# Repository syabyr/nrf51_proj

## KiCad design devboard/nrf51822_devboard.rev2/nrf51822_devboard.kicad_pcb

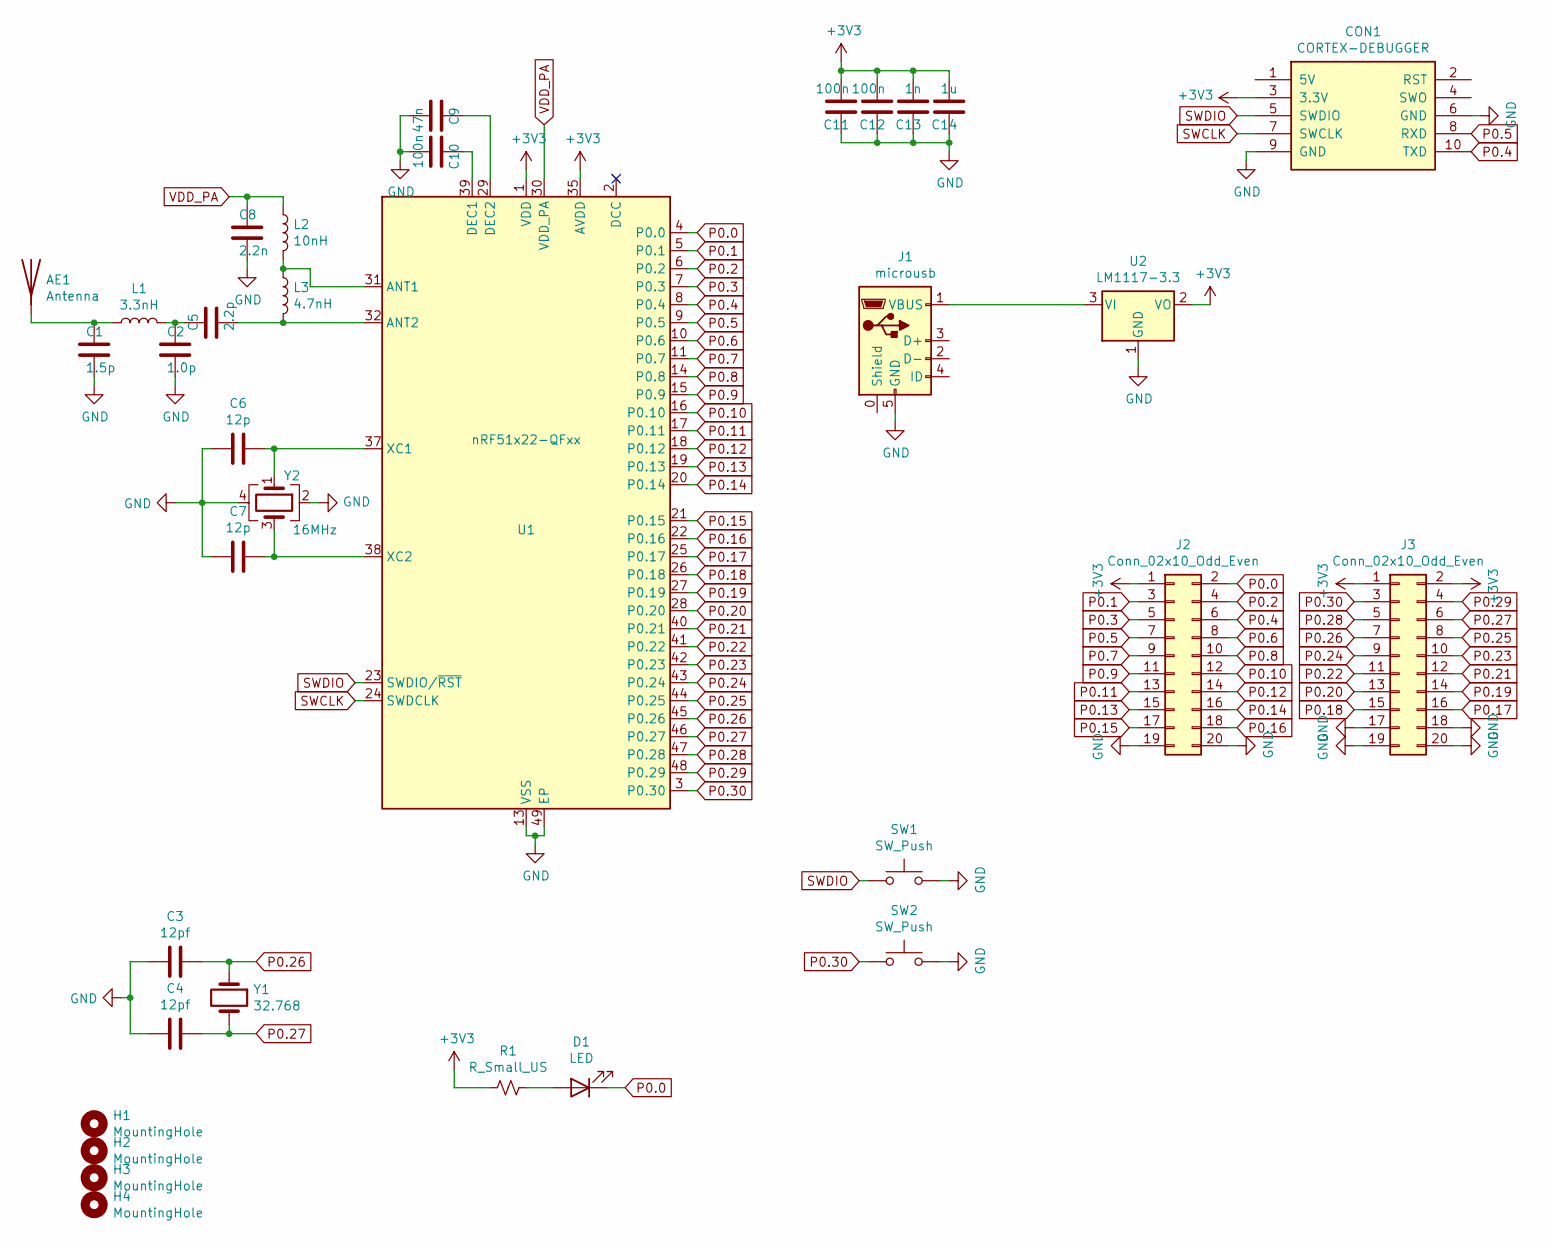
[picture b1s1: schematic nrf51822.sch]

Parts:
AE1: Antenna; Johanson_2450AT43F0100
C1: 1.5p; C_0402_1005Metric_Pad0.74x0.62mm_HandSolder
C2: 1.0p; C_0402_1005Metric_Pad0.74x0.62mm_HandSolder
C3, C4: 12pf; C_0402_1005Metric_Pad0.74x0.62mm_HandSolder
C5: 2.2p; C_0402_1005Metric_Pad0.74x0.62mm_HandSolder
C6, C7: 12p; C_0402_1005Metric_Pad0.74x0.62mm_HandSolder
C8: 2.2n; C_0402_1005Metric_Pad0.74x0.62mm_HandSolder
C9: 47n; C_0402_1005Metric_Pad0.74x0.62mm_HandSolder
C10, C11, C12: 100n; C_0402_1005Metric_Pad0.74x0.62mm_HandSolder
C13: 1n; C_0402_1005Metric_Pad0.74x0.62mm_HandSolder
C14: 1u; C_0603_1608Metric_Pad1.08x0.95mm_HandSolder
CON1: CORTEX-DEBUGGER; debugger_2x05_P1.27mm_Vertical
D1: LED; LED_0603_1608Metric_Pad1.05x0.95mm_HandSolder
H1, H2, H3, H4: MountingHole; MountingHole_3.2mm_M3_ISO7380
J1: microusb; USB_Micro-B_Wuerth_629105150521_CircularHoles
J2, J3: Conn_02x10_Odd_Even; PinHeader_2x10_P2.54mm_Vertical
L1: 3.3nH; L_0402_1005Metric_Pad0.77x0.64mm_HandSolder
L2: 10nH; L_0402_1005Metric_Pad0.77x0.64mm_HandSolder
L3: 4.7nH; L_0402_1005Metric_Pad0.77x0.64mm_HandSolder
R1: R_Small_US; R_0402_1005Metric_Pad0.72x0.64mm_HandSolder
SW1, SW2: SW_Push; turtlekey
U1: nRF51x22-QFxx; QFN-48-1EP_6x6mm_P0.4mm_EP4.6x4.6mm
U2: LM1117-3.3; SOT-223-3_TabPin2
Y1: 32.768; Crystal_SMD_G8-2Pin_3.2x1.5mm_HandSoldering
Y2: 16MHz; Crystal_SMD_3225-4Pin_3.2x2.5mm

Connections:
+3V3: C11.2, C12.2, C13.2, C14.2, CON1.3 (3.3V), J2.1, J3.1, J3.2, R1.2, U1.1 (VDD), U1.12 (VDD), U1.35 (AVDD), U1.36 (AVDD), U2.2 (VO)
GND: C1.2, C2.2, C3.2, C4.2, C6.2, C7.2, C8.2, C9.2, C10.2, C11.1, C12.1, C13.1, C14.1, CON1.6 (GND), CON1.9 (GND), J1.5 (GND), J2.19, J2.20, J3.17, J3.18, J3.19, J3.20, SW1.2, SW2.2, U1.13 (VSS), U1.33 (VSS), U1.34 (VSS), U1.49 (EP), U2.1 (GND), Y2.2, Y2.4
unnamed: AE1.1, C1.1, L1.1
unnamed: C2.1, C5.1, L1.2
unnamed: C5.2, L3.2, U1.32 (ANT2)
unnamed: C6.1, U1.37 (XC1), Y2.1
unnamed: C7.1, U1.38 (XC2), Y2.3
unnamed: C9.1, U1.29 (DEC2)
unnamed: C10.1, U1.39 (DEC1)
unnamed: D1.2 (A), R1.1
unnamed: J1.1 (VBUS), U2.3 (VI)
unnamed: L2.2, L3.1, U1.31 (ANT1)
P0.0: D1.1 (K), J2.2, U1.4 (P0.0)
P0.1: J2.3, U1.5 (P0.1)
P0.2: J2.4, U1.6 (P0.2)
P0.3: J2.5, U1.7 (P0.3)
P0.4: CON1.10 (TXD), J2.6, U1.8 (P0.4)
P0.5: CON1.8 (RXD), J2.7, U1.9 (P0.5)
P0.6: J2.8, U1.10 (P0.6)
P0.7: J2.9, U1.11 (P0.7)
P0.8: J2.10, U1.14 (P0.8)
P0.9: J2.11, U1.15 (P0.9)
P0.10: J2.12, U1.16 (P0.10)
P0.11: J2.13, U1.17 (P0.11)
P0.12: J2.14, U1.18 (P0.12)
P0.13: J2.15, U1.19 (P0.13)
P0.14: J2.16, U1.20 (P0.14)
P0.15: J2.17, U1.21 (P0.15)
P0.16: J2.18, U1.22 (P0.16)
P0.17: J3.16, U1.25 (P0.17)
P0.18: J3.15, U1.26 (P0.18)
P0.19: J3.14, U1.27 (P0.19)
P0.20: J3.13, U1.28 (P0.20)
P0.21: J3.12, U1.40 (P0.21)
P0.22: J3.11, U1.41 (P0.22)
P0.23: J3.10, U1.42 (P0.23)
P0.24: J3.9, U1.43 (P0.24)
P0.25: J3.8, U1.44 (P0.25)
P0.26: C3.1, J3.7, U1.45 (P0.26), Y1.1
P0.27: C4.1, J3.6, U1.46 (P0.27), Y1.2
P0.28: J3.5, U1.47 (P0.28)
P0.29: J3.4, U1.48 (P0.29)
P0.30: J3.3, SW2.1, U1.3 (P0.30)
SWCLK: CON1.7 (SWCLK), U1.24 (SWDCLK)
SWDIO: CON1.5 (SWDIO), SW1.1, U1.23 (SWDIO/~RST)
VDD_PA: C8.1, L2.1, U1.30 (VDD_PA)

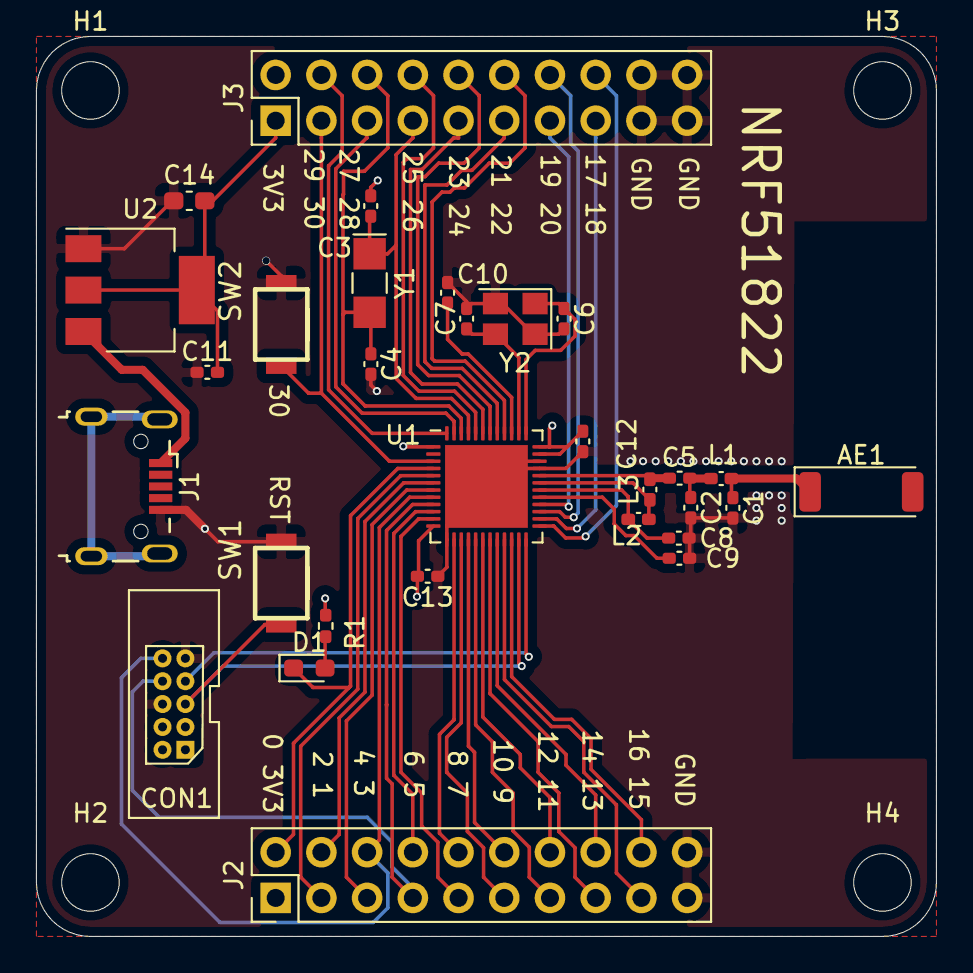
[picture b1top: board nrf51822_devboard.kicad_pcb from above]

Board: 4 copper layers, 50.0 x 50.0 mm, 34 parts (0 on the bottom side), 46 nets.

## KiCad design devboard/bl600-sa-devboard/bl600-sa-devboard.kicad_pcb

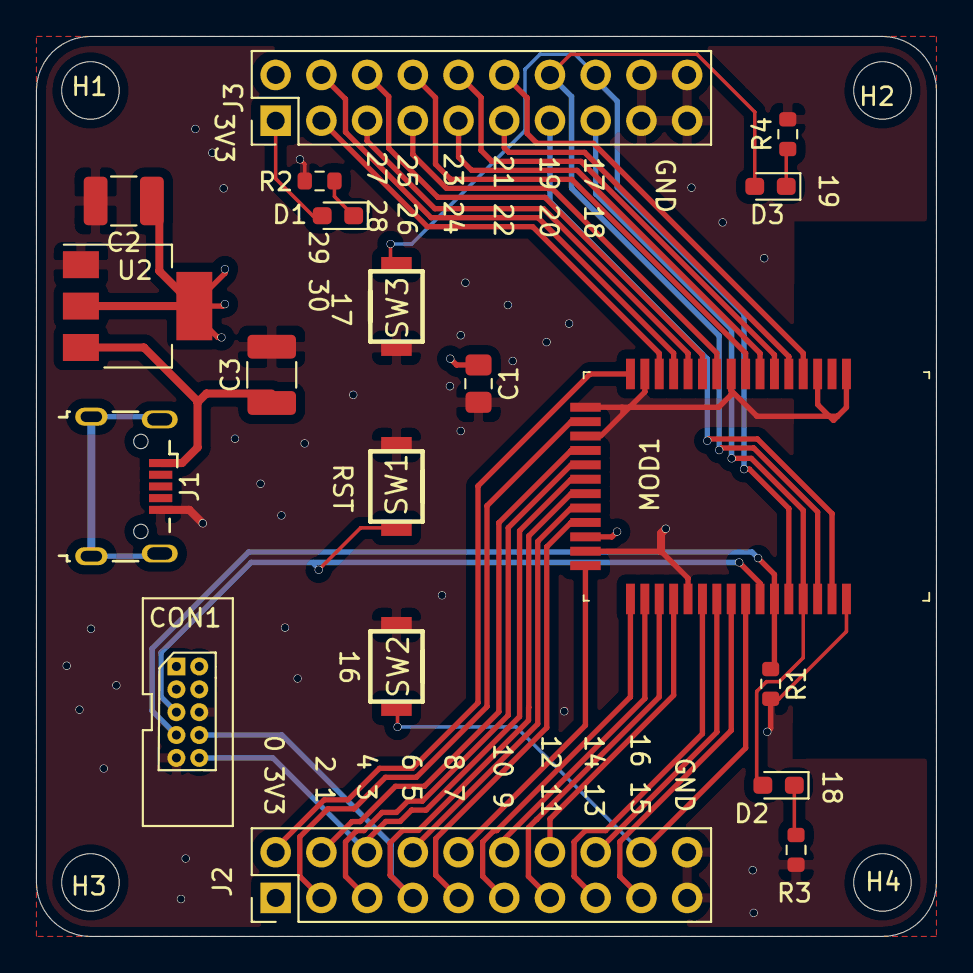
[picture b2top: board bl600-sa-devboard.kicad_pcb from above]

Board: 4 copper layers, 50.0 x 50.0 mm, 23 parts (0 on the bottom side), 39 nets.

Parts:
C1: C_Small; C_0805_2012Metric_Pad1.18x1.45mm_HandSolder
C2, C3: C_Small; C_1210_3225Metric_Pad1.33x2.70mm_HandSolder
CON1: CORTEX-DEBUGGER; debugger_2x05_P1.27mm_Vertical
D1, D2, D3: LED; LED_0603_1608Metric_Pad1.05x0.95mm_HandSolder
H1, H2, H3, H4: MountingHole; MountingHole_3.2mm_M3
J1: microusb; USB_Micro-B_Wuerth_629105150521_CircularHoles
J2, J3: Conn_02x10_Odd_Even; PinHeader_2x10_P2.54mm_Vertical
MOD1: BL600-SA; BLUETOOTH_MODULE_BL600-SA
R1, R2, R3, R4: 12K; R_0603_1608Metric
SW1, SW2, SW3: SW_Push; turtlekey
U2: LM1117-3.3; SOT-223-3_TabPin2

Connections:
+3V3: C1.1, C2.1, CON1.3, D1.2, J2.1, J3.1, J3.2, MOD1.10, U2.2
GND: C1.2, C2.2, C3.2, CON1.6, CON1.9, J1.5, J2.19, J2.20, J3.17, J3.18, J3.19, J3.20, MOD1.1, MOD1.3, MOD1.11, MOD1.17, MOD1.28, MOD1.29, MOD1.31, MOD1.37, MOD1.43, R1.2, R2.2, R3.2, R4.2, SW1.2, SW2.2, SW3.2, U2.1
IO_0: J2.2, MOD1.44
IO_1: J2.3, MOD1.2
IO_2: J2.4, MOD1.4
IO_3: J2.5, MOD1.5
IO_4: CON1.10, J2.6, MOD1.6
IO_5: CON1.8, J2.7, MOD1.7
IO_6: J2.8, MOD1.8
IO_7: J2.9, MOD1.9
IO_8: J2.10, MOD1.12
IO_9: J2.11, MOD1.13
IO_10: J2.12, MOD1.14
IO_11: J2.13, MOD1.15
IO_12: J2.14, MOD1.16
IO_13: J2.15, MOD1.18
IO_14: J2.16, MOD1.19
IO_15: J2.17, MOD1.20
IO_16: J2.18, MOD1.21, SW2.1
IO_17: J3.16, MOD1.24, SW3.1
IO_18: D2.2, J3.15, MOD1.25
IO_19: D3.2, J3.14, MOD1.26
IO_20: J3.13, MOD1.27
IO_21: J3.12, MOD1.32
IO_22: J3.11, MOD1.33
IO_23: J3.10, MOD1.34
IO_24: J3.9, MOD1.35
IO_25: J3.8, MOD1.36
IO_26: J3.7, MOD1.38
IO_27: J3.6, MOD1.39
IO_28: J3.5, MOD1.40
IO_29: J3.4, MOD1.41
IO_30: J3.3, MOD1.42
unnamed: D1.1, R2.1
unnamed: D2.1, R3.1
unnamed: D3.1, R4.1
SWCLK: CON1.7, MOD1.23, R1.1
SWDIO: CON1.5, MOD1.22, SW1.1
VBUS: C3.1, J1.1, U2.3

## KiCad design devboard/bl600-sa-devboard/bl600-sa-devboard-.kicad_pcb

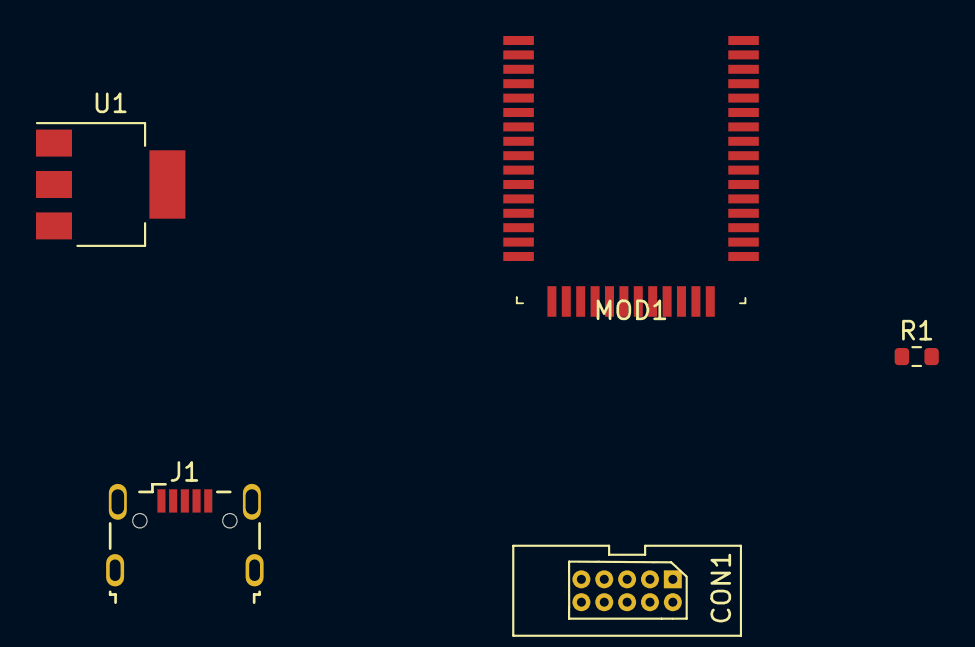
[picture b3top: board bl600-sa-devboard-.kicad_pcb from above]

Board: 2 copper layers, 5 parts (0 on the bottom side), 7 nets, no tracks yet.

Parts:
CON1: CORTEX-DEBUGGER; debugger_2x05_P1.27mm_Vertical
J1: microusb; USB_Micro-B_Wuerth_629105150521_CircularHoles
MOD1: BL600-SA; BLUETOOTH_MODULE_BL600-SA
R1: 12K; R_0603_1608Metric
U1: LM1117-3.3; SOT-223-3_TabPin2

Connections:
+3V3: CON1.3, MOD1.10, U1.2
GND: CON1.6, CON1.9, J1.5, MOD1.1, MOD1.3, MOD1.11, MOD1.17, MOD1.28, MOD1.29, MOD1.31, MOD1.37, MOD1.43, R1.2, U1.1
IO_4: CON1.10, MOD1.6
IO_5: CON1.8, MOD1.7
SWCLK: CON1.7, MOD1.23, R1.1
SWDIO: CON1.5, MOD1.22
VBUS: J1.1, U1.3

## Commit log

2021-12-09 orig
2021-12-09 helloworld
2021-12-09 cmake
2021-12-10 ld fix
2021-12-10 ble ok
2022-01-30 devboard
2022-10-14 microbit
2022-10-14 proj
2023-04-09 hinata
2023-04-14 nrf51_sdk-11.0.0
2023-04-14 blink
2023-04-15 ds18b20
2025-01-28 Update Makefile
2025-01-28 makefile
2025-04-03 no board depend
2025-04-03 uart
2025-04-03 ignore
2025-04-03 bl600
2025-12-02 remove pio
